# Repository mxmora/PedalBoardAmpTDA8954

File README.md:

# PedalBoardAmpTDA8954
PedalBoardAmpTDA8954

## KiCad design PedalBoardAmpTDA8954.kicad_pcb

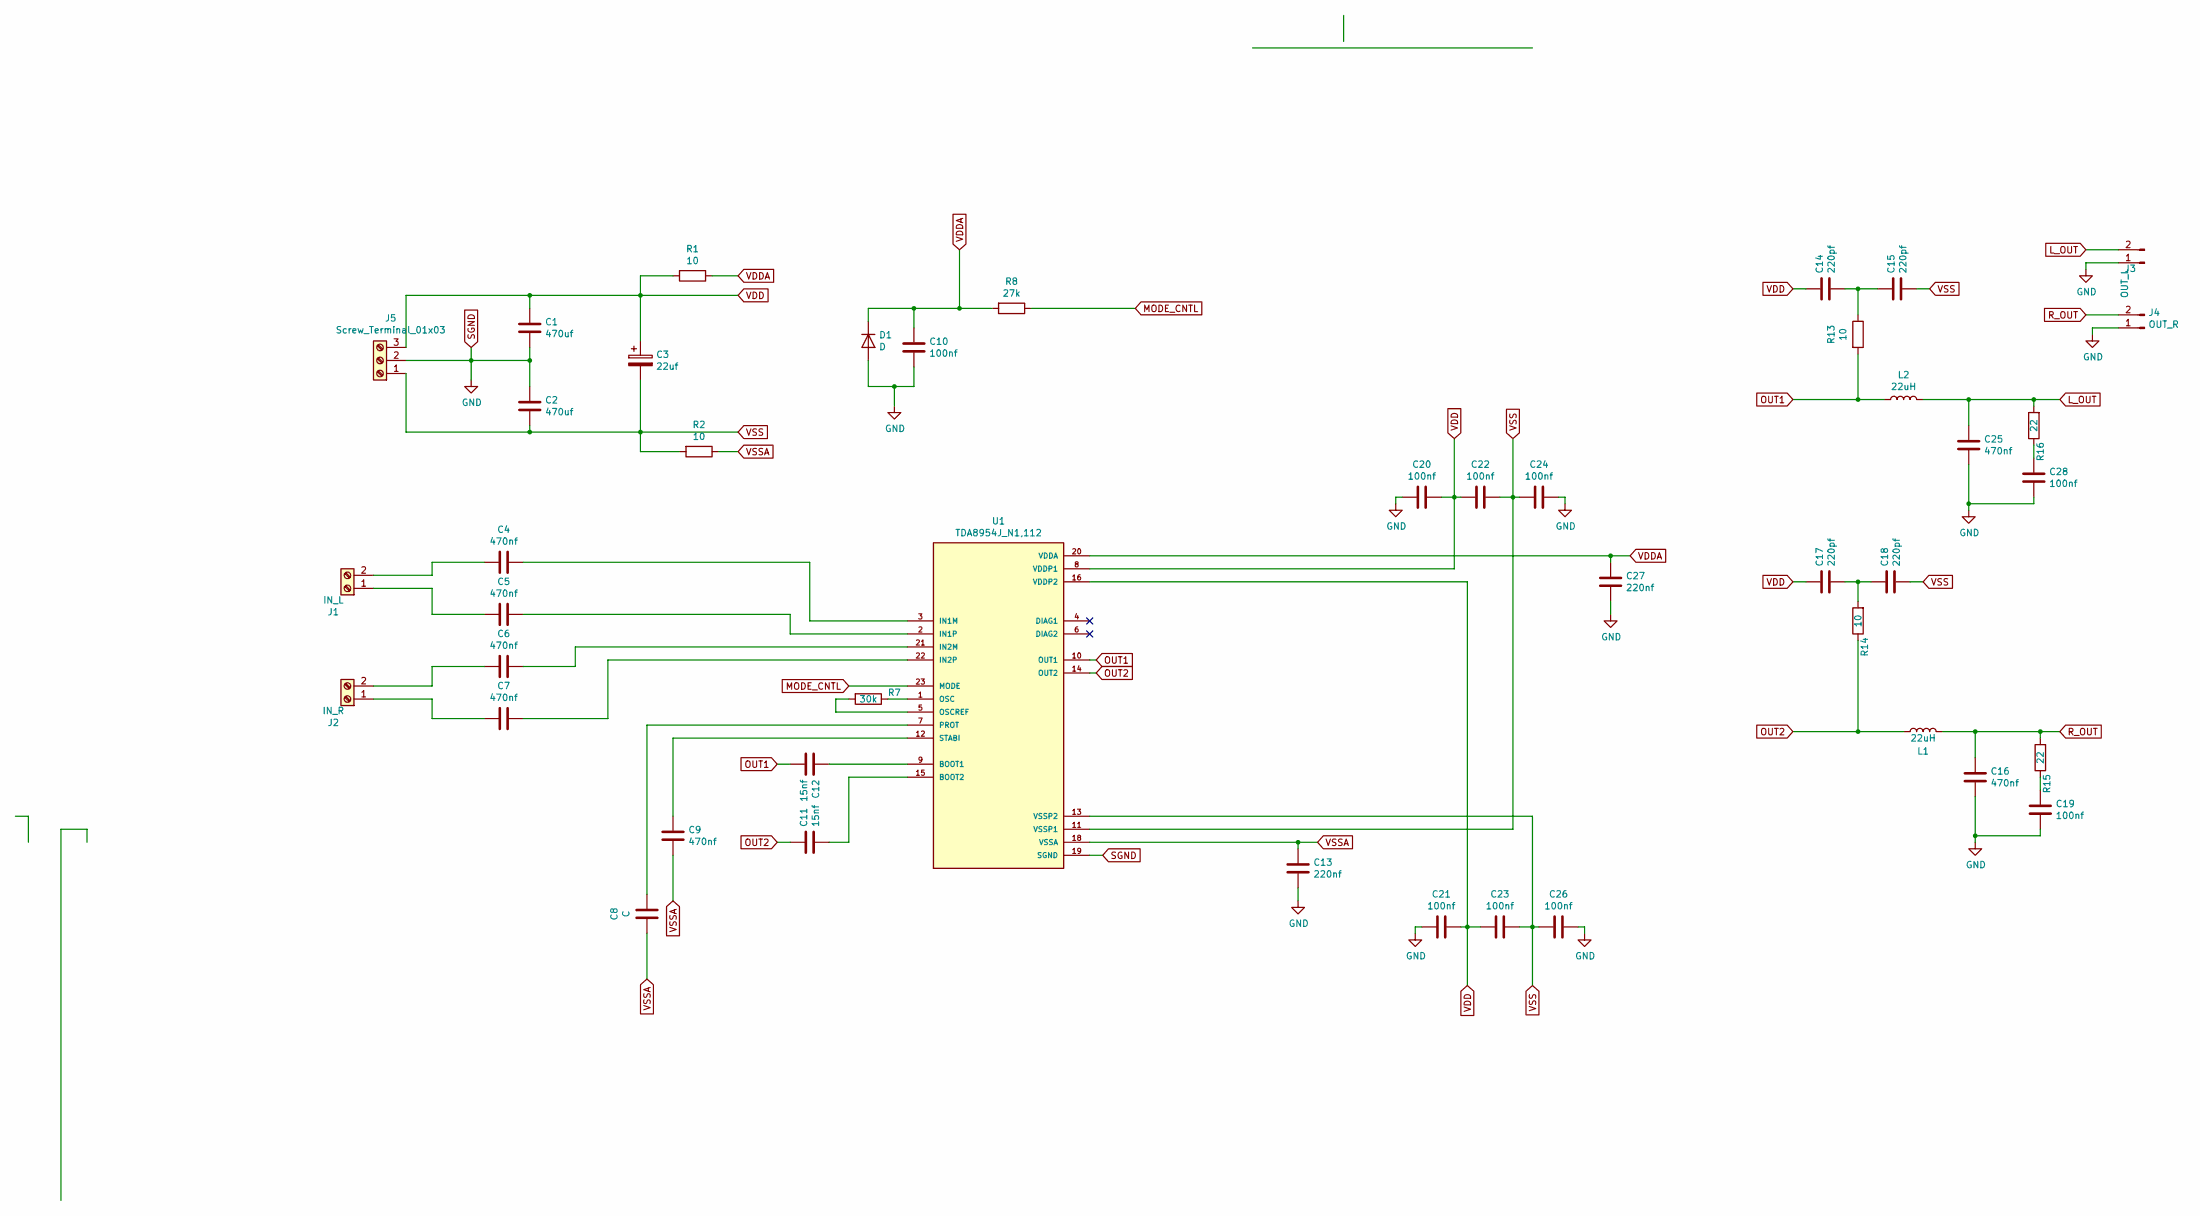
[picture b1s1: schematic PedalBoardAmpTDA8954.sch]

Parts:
C1, C2: 470uf; CP_Radial_D12.5mm_P5.00mm
C3: 22uf; CP_Radial_D10.0mm_P5.00mm
C4, C5, C6, C7, C9, C16, C25: 470nf; C_Rect_L7.0mm_W2.0mm_P5.00mm
C8: C; C_Rect_L7.0mm_W2.0mm_P5.00mm
C10, C19, C20, C21, C22, C23, C24, C26, C28: 100nf; C_Rect_L7.0mm_W2.0mm_P5.00mm
C11, C12: 15nf; C_Rect_L7.0mm_W2.0mm_P5.00mm
C13, C27: 220nf; C_Rect_L7.0mm_W2.0mm_P5.00mm
C14, C15, C17, C18: 220pf; C_Rect_L7.0mm_W2.0mm_P5.00mm
D1: D; D_DO-35_SOD27_P7.62mm_Horizontal
J1: IN_L; TerminalBlock_RND_205-00001_1x02_P5.00mm_Horizontal
J2: IN_R; TerminalBlock_RND_205-00001_1x02_P5.00mm_Horizontal
J3: OUT_L; TerminalBlock_RND_205-00045_1x02_P5.00mm_Horizontal
J4: OUT_R; TerminalBlock_RND_205-00045_1x02_P5.00mm_Horizontal
J5: Screw_Terminal_01x03; TerminalBlock_RND_205-00046_1x03_P5.00mm_Horizontal
L1, L2: 22uH; L_Toroid_Vertical_L21.6mm_W8.4mm_P8.38mm_Pulse_G
R1, R2, R13, R14: 10; R_Axial_DIN0207_L6.3mm_D2.5mm_P7.62mm_Horizontal
R7: 30k; R_Axial_DIN0207_L6.3mm_D2.5mm_P7.62mm_Horizontal
R8: 27k; R_Axial_DIN0207_L6.3mm_D2.5mm_P7.62mm_Horizontal
R15, R16: 22; R_Radial_Power_L13.0mm_W9.0mm_P5.00mm
U1: TDA8954J_N1,112; SOT411-1

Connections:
L_OUT: C25.1, J3.2, L2.2, R16.2
MODE_CNTL: R8.1, U1.23 (MODE)
unnamed: C4.1, U1.3 (IN1M)
unnamed: C4.2, J1.2
unnamed: C5.1, U1.2 (IN1P)
unnamed: C5.2, J1.1
unnamed: C6.1, U1.21 (IN2M)
unnamed: C6.2, J2.2
unnamed: C7.1, U1.22 (IN2P)
unnamed: C7.2, J2.1
unnamed: C8.1, U1.7 (PROT)
unnamed: C9.2, U1.12 (STABI)
unnamed: C11.2, U1.15 (BOOT2)
unnamed: C12.1, U1.9 (BOOT1)
unnamed: C14.2, C15.1, R13.1
unnamed: C17.1, C18.2, R14.2
unnamed: C19.1, R15.1
unnamed: C28.1, R16.1
unnamed: R7.1, U1.1 (OSC)
unnamed: R7.2, U1.5 (OSCREF)
OUT1: C12.2, L2.1, R13.2, U1.10 (OUT1)
OUT2: C11.1, L1.1, R14.1, U1.14 (OUT2)
R_OUT: C16.1, J4.2, L1.2, R15.2
SGND: C1.2, C2.1, C10.2, C13.2, C16.2, C19.2, C20.2, C21.2, C24.1, C25.2, C26.1, C27.2, C28.2, D1.2 (A), J3.1, J4.1, J5.2, U1.19 (SGND)
VDD: C1.1, C3.1, C14.1, C17.2, C20.1, C21.1, C22.1, C23.2, J5.3, R1.2, U1.8 (VDDP1), U1.16 (VDDP2)
VDDA: C10.1, C27.1, D1.1 (K), R1.1, R8.2, U1.20 (VDDA)
VSS: C2.2, C3.2, C15.2, C18.1, C22.2, C23.1, C24.2, C26.2, J5.1, R2.2, U1.11 (VSSP1), U1.13 (VSSP2)
VSSA: C8.2, C9.1, C13.1, R2.1, U1.18 (VSSA)

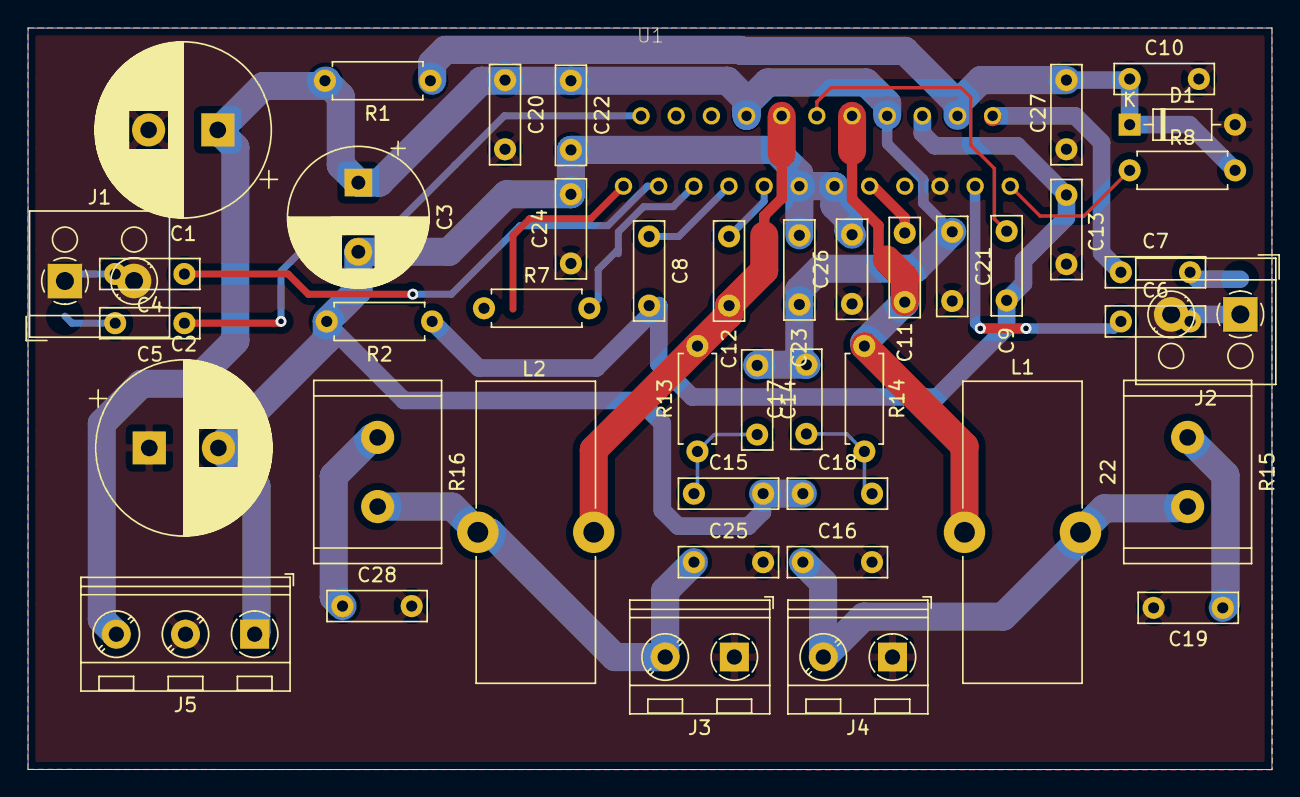
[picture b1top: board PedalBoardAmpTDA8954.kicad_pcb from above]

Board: 2 copper layers, 89.9 x 53.6 mm, 45 parts (0 on the bottom side), 28 nets.

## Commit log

2021-01-05 first check in
